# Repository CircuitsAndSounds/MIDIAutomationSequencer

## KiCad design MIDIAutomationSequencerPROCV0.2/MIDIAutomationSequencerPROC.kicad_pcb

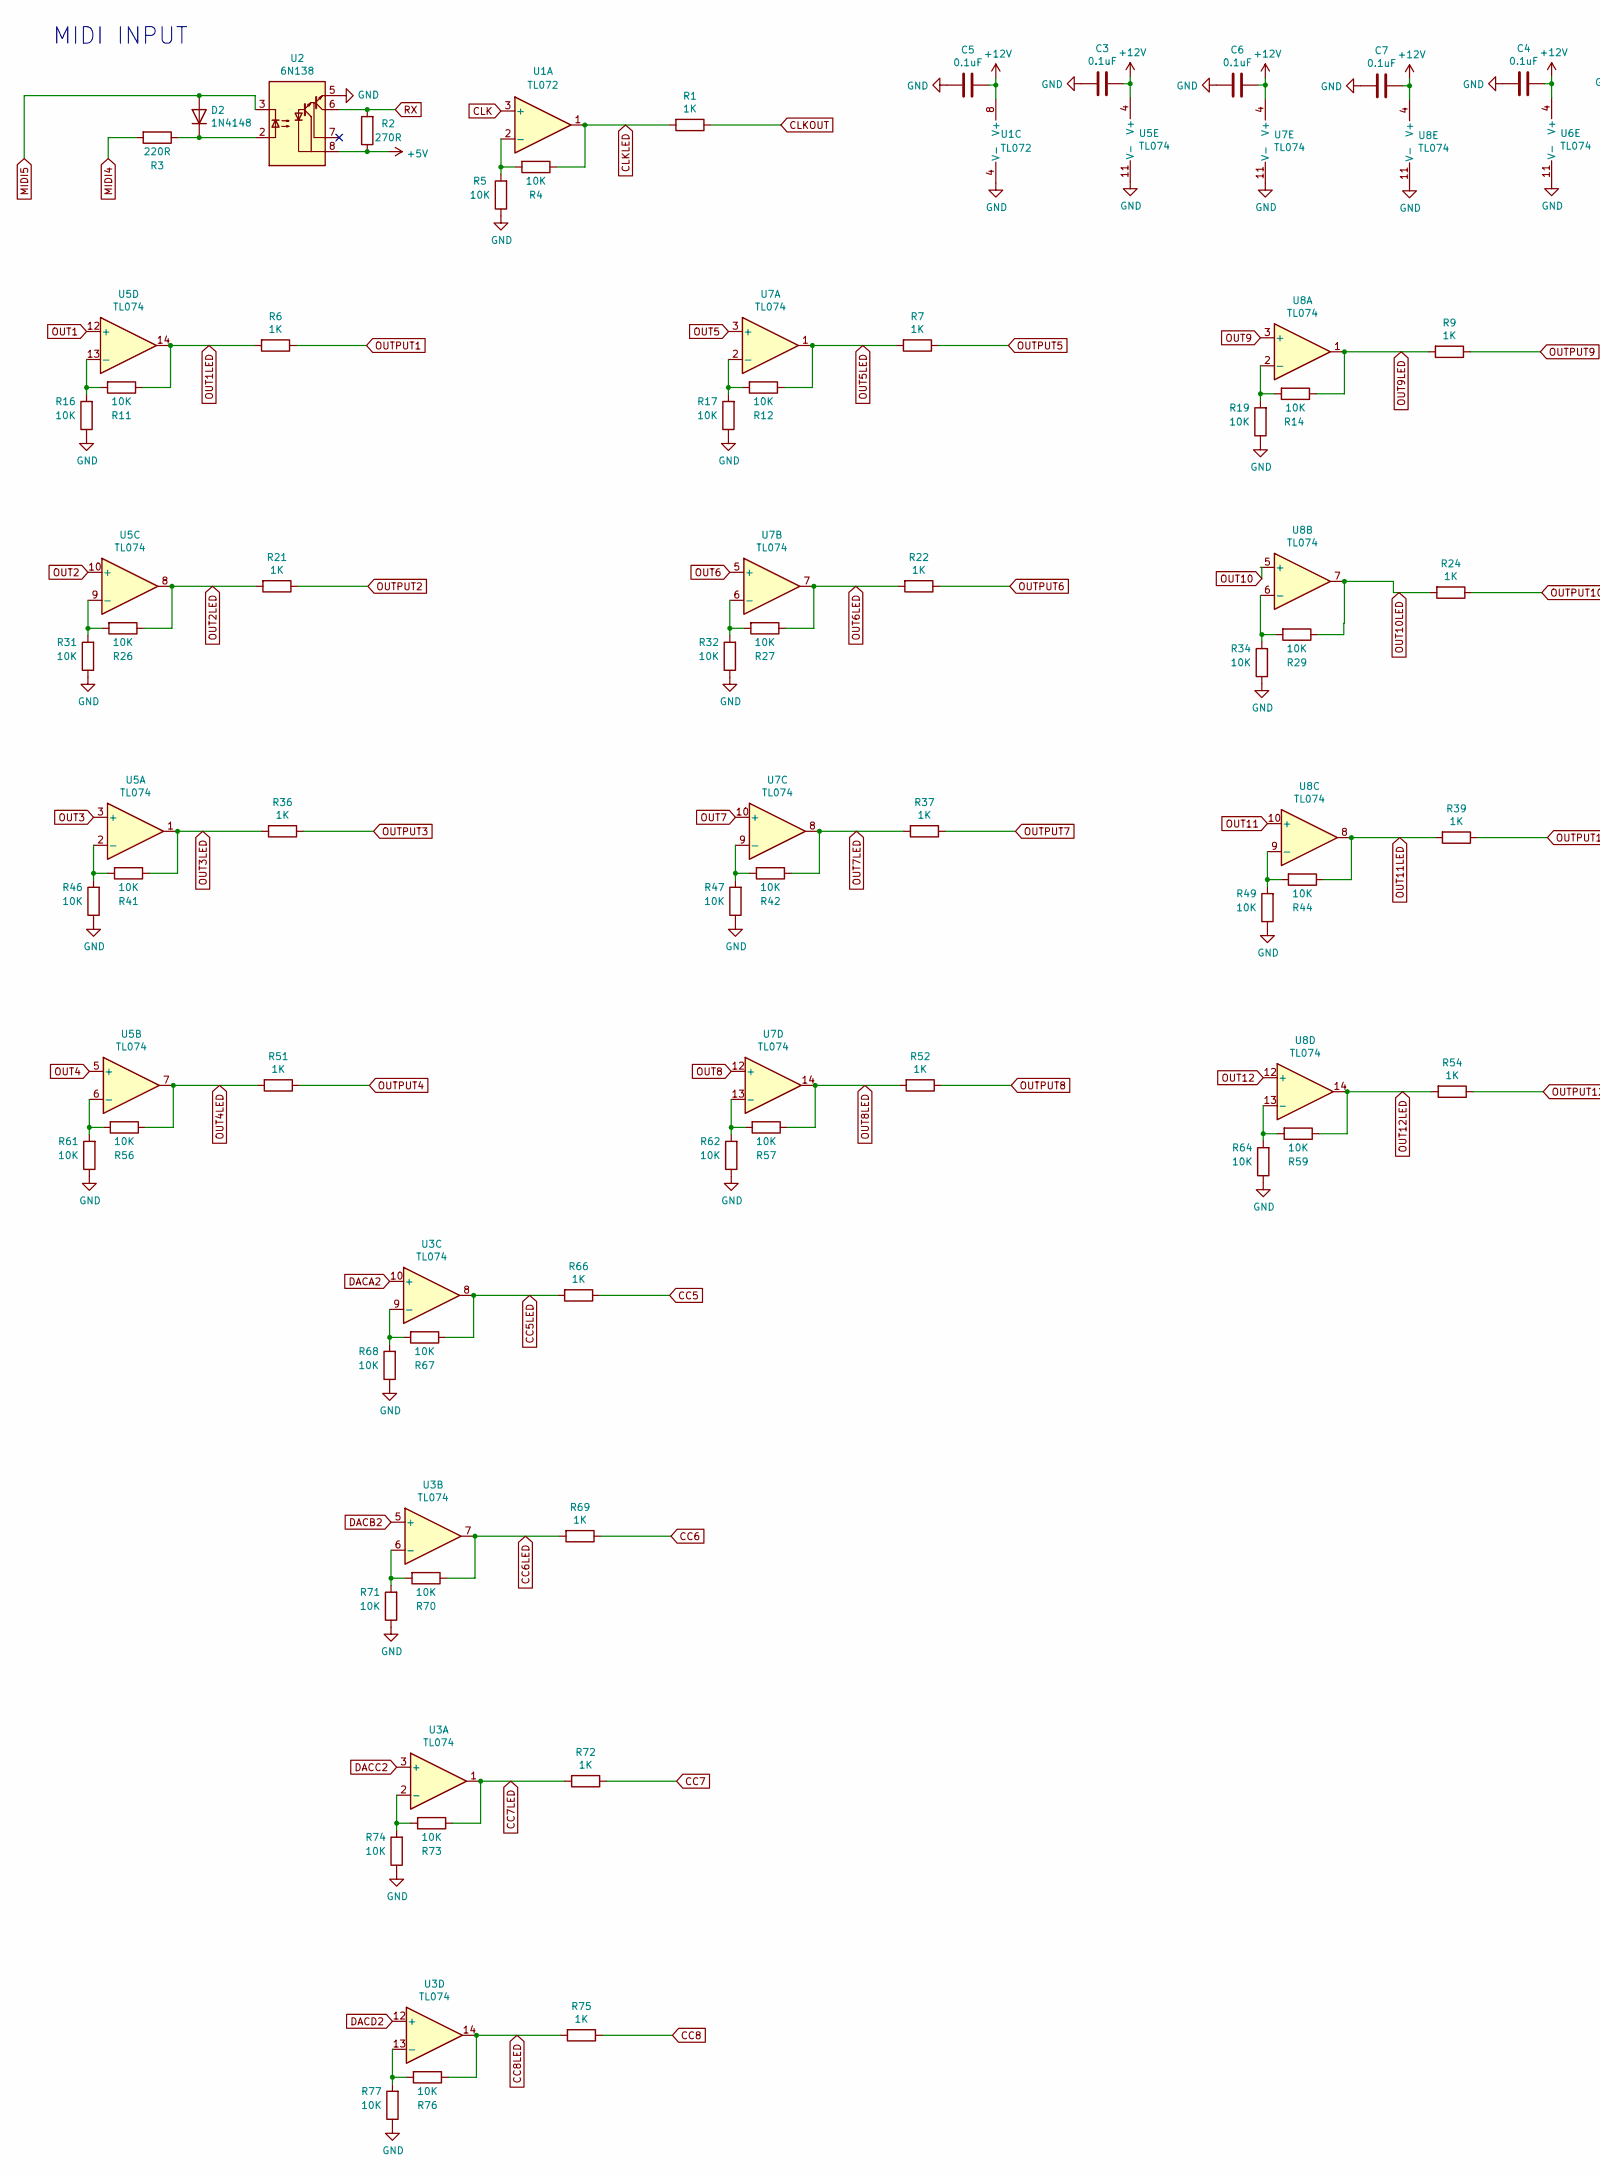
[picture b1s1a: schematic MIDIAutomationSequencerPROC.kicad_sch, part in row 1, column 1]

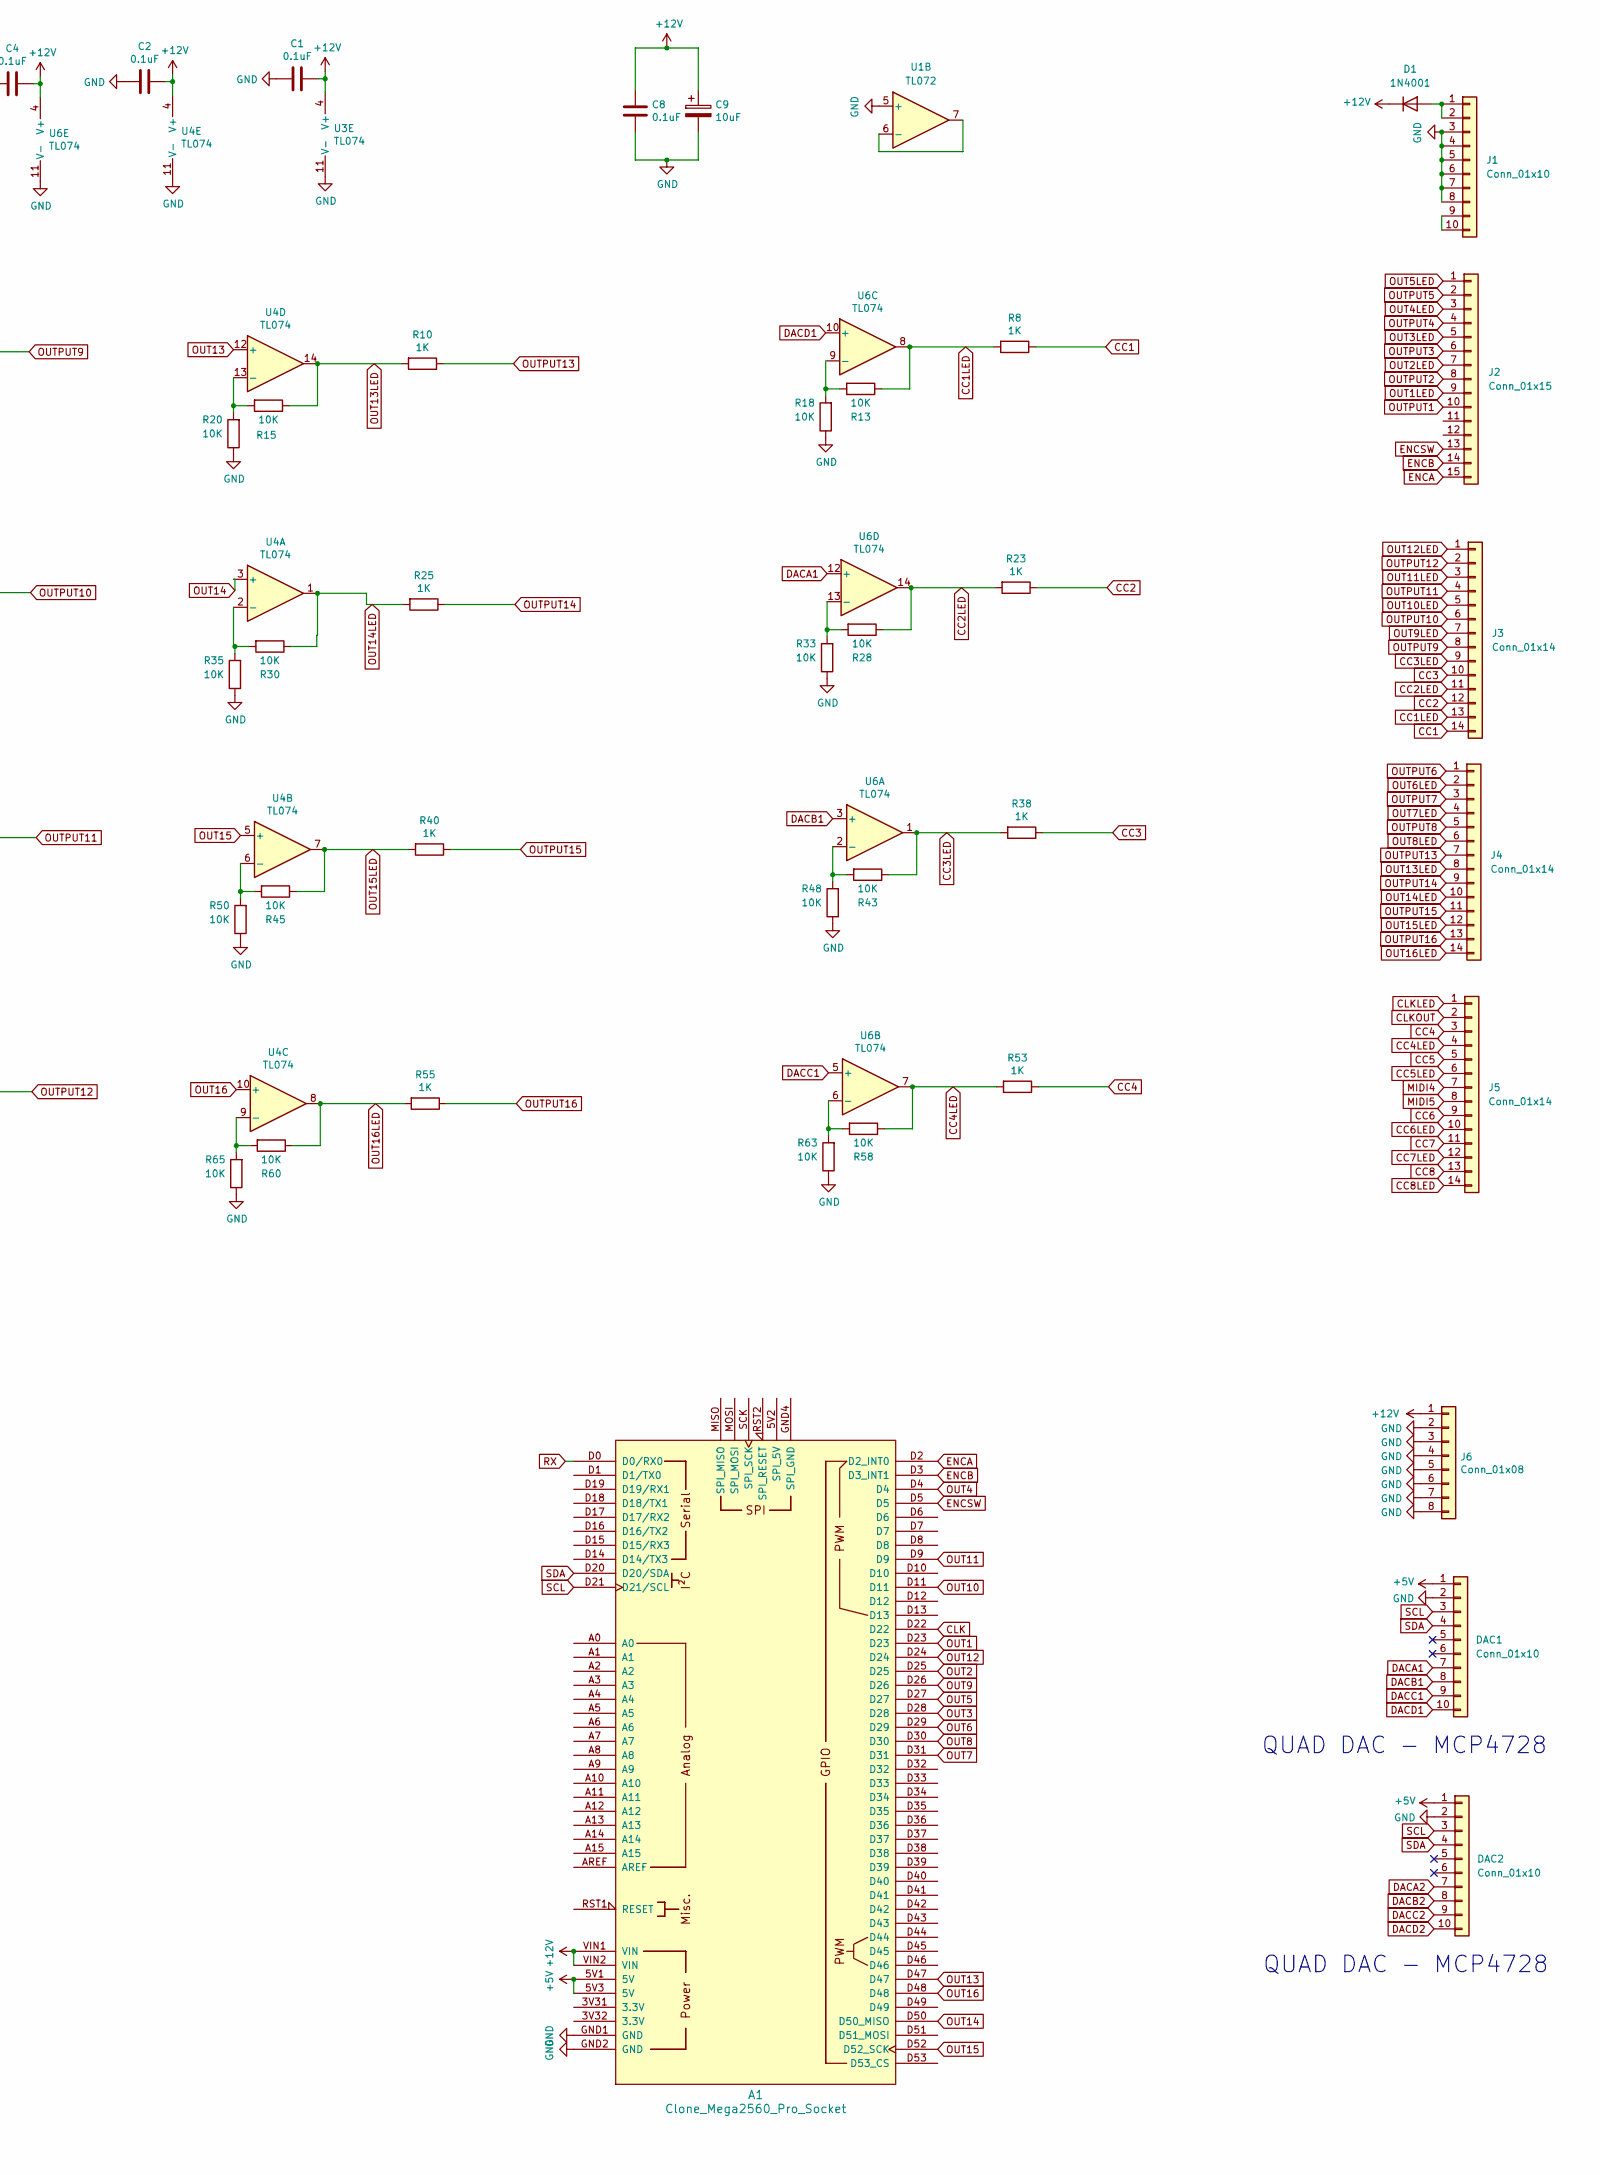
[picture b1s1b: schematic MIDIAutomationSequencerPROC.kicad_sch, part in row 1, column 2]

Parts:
A1: Clone_Mega2560_Pro_Socket
C1, C2, C3, C4, C5, C6, C7, C8: 0.1uF; C_Rect_L7.0mm_W2.0mm_P5.00mm
C9: 10uF; CP_Radial_D5.0mm_P2.50mm
D1: 1N4001; D_DO-41_SOD81_P10.16mm_Horizontal
D2: 1N4148; D_DO-35_SOD27_P2.54mm_Vertical_AnodeUp
DAC1, DAC2: Conn_01x10; PinHeader_1x10_P2.54mm_Vertical
J1: Conn_01x10; PinHeader_2x05_P2.54mm_Vertical
J2: Conn_01x15; PinHeader_1x15_P2.54mm_Vertical
J3, J4, J5: Conn_01x14; PinHeader_1x14_P2.54mm_Vertical
J6: Conn_01x08; PinHeader_1x08_P2.54mm_Vertical
R1, R6, R7, R8, R9, R10, R21, R22, R23, R24, R25, R36, R37, R38, R39, R40, R51, R52, R53, R54, R55, R66, R69, R72, R75: 1K; R_Axial_DIN0207_L6.3mm_D2.5mm_P2.54mm_Vertical
R2: 270R; R_Axial_DIN0207_L6.3mm_D2.5mm_P2.54mm_Vertical
R3: 220R; R_Axial_DIN0207_L6.3mm_D2.5mm_P2.54mm_Vertical
R4, R5, R11, R12, R13, R14, R15, R16, R17, R18, R19, R20, R26, R27, R28, R29, R30, R31, R32, R33, R34, R35, R41, R42, R43, R44, R45, R46, R47, R48, R49, R50, R56, R57, R58, R59, R60, R61, R62, R63, R64, R65, R67, R68, R70, R71, R73, R74, R76, R77: 10K; R_Axial_DIN0207_L6.3mm_D2.5mm_P2.54mm_Vertical
U1: TL072; DIP-8_W7.62mm
U2: 6N138; DIP-8_W7.62mm
U3, U4, U5, U6, U7, U8: TL074; DIP-14_W7.62mm

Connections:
+5V: A1.5V1 (5V), A1.5V3 (5V), DAC1.1, DAC2.1, R2.1, U2.8 (VCC)
+12V: A1.VIN1 (VIN), A1.VIN2 (VIN), C1.1, C2.1, C3.1, C4.1, C5.1, C6.1, C7.1, C8.1, C9.1, D1.1 (K), J6.1, U1.8 (V+), U3.4 (V+), U4.4 (V+), U5.4 (V+), U6.4 (V+), U7.4 (V+), U8.4 (V+)
CC1: J3.14, R8.1
CC1LED: J3.13, R8.2, R13.1, U6.8
CC2: J3.12, R23.1
CC2LED: J3.11, R23.2, R28.1, U6.14
CC3: J3.10, R38.1
CC3LED: J3.9, R38.2, R43.1, U6.1
CC4: J5.3, R53.1
CC4LED: J5.4, R53.2, R58.1, U6.7
CC5: J5.5, R66.1
CC5LED: J5.6, R66.2, R67.1, U3.8
CC6: J5.9, R69.1
CC6LED: J5.10, R69.2, R70.1, U3.7
CC7: J5.11, R72.1
CC7LED: J5.12, R72.2, R73.1, U3.1
CC8: J5.13, R75.1
CC8LED: J5.14, R75.2, R76.1, U3.14
CLK: A1.D22, U1.3 (+)
CLKLED: J5.1, R1.2, R4.1, U1.1
CLKOUT: J5.2, R1.1
DACA1: DAC1.7, U6.12 (+)
DACA2: DAC2.7, U3.10 (+)
DACB1: DAC1.8, U6.3 (+)
DACB2: DAC2.8, U3.5 (+)
DACC1: DAC1.9, U6.5 (+)
DACC2: DAC2.9, U3.3 (+)
DACD1: DAC1.10, U6.10 (+)
DACD2: DAC2.10, U3.12 (+)
ENCA: A1.D2 (D2_INT0), J2.15
ENCB: A1.D3 (D3_INT1), J2.14
ENCSW: A1.D5, J2.13
GND: A1.GND1 (GND), A1.GND2 (GND), C1.2, C2.2, C3.2, C4.2, C5.2, C6.2, C7.2, C8.2, C9.2, DAC1.2, DAC2.2, J1.3, J1.4, J1.5, J1.6, J1.7, J1.8, J6.2, J6.3, J6.4, J6.5, J6.6, J6.7, J6.8, R5.1, R16.1, R17.1, R18.1, R19.1, R20.1, R31.1, R32.1, R33.1, R34.1, R35.1, R46.1, R47.1, R48.1, R49.1, R50.1, R61.1, R62.1, R63.1, R64.1, R65.1, R68.1, R71.1, R74.1, R77.1, U1.4 (V-), U1.5 (+), U2.5 (GND), U3.11 (V-), U4.11 (V-), U5.11 (V-), U6.11 (V-), U7.11 (V-), U8.11 (V-)
MIDI4: J5.7, R3.2
MIDI5: D2.2 (A), J5.8, U2.3 (C2)
unnamed: D1.2 (A), J1.1, J1.2
unnamed: D2.1 (K), R3.1, U2.2 (C1)
unnamed: J1.9, J1.10
unnamed: R4.2, R5.2, U1.2 (-)
unnamed: U1.6 (-), U1.7
unnamed: R73.2, R74.2, U3.2 (-)
unnamed: R70.2, R71.2, U3.6 (-)
unnamed: R67.2, R68.2, U3.9 (-)
unnamed: R76.2, R77.2, U3.13 (-)
unnamed: R30.2, R35.2, U4.2 (-)
unnamed: R45.2, R50.2, U4.6 (-)
unnamed: R60.2, R65.2, U4.9 (-)
unnamed: R15.2, R20.2, U4.13 (-)
unnamed: R41.2, R46.2, U5.2 (-)
unnamed: R56.2, R61.2, U5.6 (-)
unnamed: R26.2, R31.2, U5.9 (-)
unnamed: R11.2, R16.2, U5.13 (-)
unnamed: R43.2, R48.2, U6.2 (-)
unnamed: R58.2, R63.2, U6.6 (-)
unnamed: R13.2, R18.2, U6.9 (-)
unnamed: R28.2, R33.2, U6.13 (-)
unnamed: R12.2, R17.2, U7.2 (-)
unnamed: R27.2, R32.2, U7.6 (-)
unnamed: R42.2, R47.2, U7.9 (-)
unnamed: R57.2, R62.2, U7.13 (-)
unnamed: R14.2, R19.2, U8.2 (-)
unnamed: R29.2, R34.2, U8.6 (-)
unnamed: R44.2, R49.2, U8.9 (-)
unnamed: R59.2, R64.2, U8.13 (-)
OUT1: A1.D23, U5.12 (+)
OUT1LED: J2.9, R6.2, R11.1, U5.14
OUT2: A1.D25, U5.10 (+)
OUT2LED: J2.7, R21.2, R26.1, U5.8
OUT3: A1.D28, U5.3 (+)
OUT3LED: J2.5, R36.2, R41.1, U5.1
OUT4: A1.D4, U5.5 (+)
OUT4LED: J2.3, R51.2, R56.1, U5.7
OUT5: A1.D27, U7.3 (+)
OUT5LED: J2.1, R7.2, R12.1, U7.1
OUT6: A1.D29, U7.5 (+)
OUT6LED: J4.2, R22.2, R27.1, U7.7
OUT7: A1.D31, U7.10 (+)
OUT7LED: J4.4, R37.2, R42.1, U7.8
OUT8: A1.D30, U7.12 (+)
OUT8LED: J4.6, R52.2, R57.1, U7.14
OUT9: A1.D26, U8.3 (+)
OUT9LED: J3.7, R9.2, R14.1, U8.1
OUT10: A1.D11, U8.5 (+)
OUT10LED: J3.5, R24.2, R29.1, U8.7
OUT11: A1.D9, U8.10 (+)
OUT11LED: J3.3, R39.2, R44.1, U8.8
OUT12: A1.D24, U8.12 (+)
OUT12LED: J3.1, R54.2, R59.1, U8.14
OUT13: A1.D47, U4.12 (+)
OUT13LED: J4.8, R10.2, R15.1, U4.14
OUT14: A1.D50 (D50_MISO), U4.3 (+)
OUT14LED: J4.10, R25.2, R30.1, U4.1
OUT15: A1.D52 (D52_SCK), U4.5 (+)
OUT15LED: J4.12, R40.2, R45.1, U4.7
OUT16: A1.D48, U4.10 (+)
OUT16LED: J4.14, R55.2, R60.1, U4.8
OUTPUT1: J2.10, R6.1
OUTPUT2: J2.8, R21.1
OUTPUT3: J2.6, R36.1
OUTPUT4: J2.4, R51.1
OUTPUT5: J2.2, R7.1
OUTPUT6: J4.1, R22.1
OUTPUT7: J4.3, R37.1
OUTPUT8: J4.5, R52.1
OUTPUT9: J3.8, R9.1
OUTPUT10: J3.6, R24.1
OUTPUT11: J3.4, R39.1
OUTPUT12: J3.2, R54.1
OUTPUT13: J4.7, R10.1
OUTPUT14: J4.9, R25.1
OUTPUT15: J4.11, R40.1
OUTPUT16: J4.13, R55.1
RX: A1.D0 (D0/RX0), R2.2, U2.6 (VO2)
SCL: A1.D21 (D21/SCL), DAC1.3, DAC2.3
SDA: A1.D20 (D20/SDA), DAC1.4, DAC2.4

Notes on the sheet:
QUAD DAC - MCP4728
MIDI INPUT

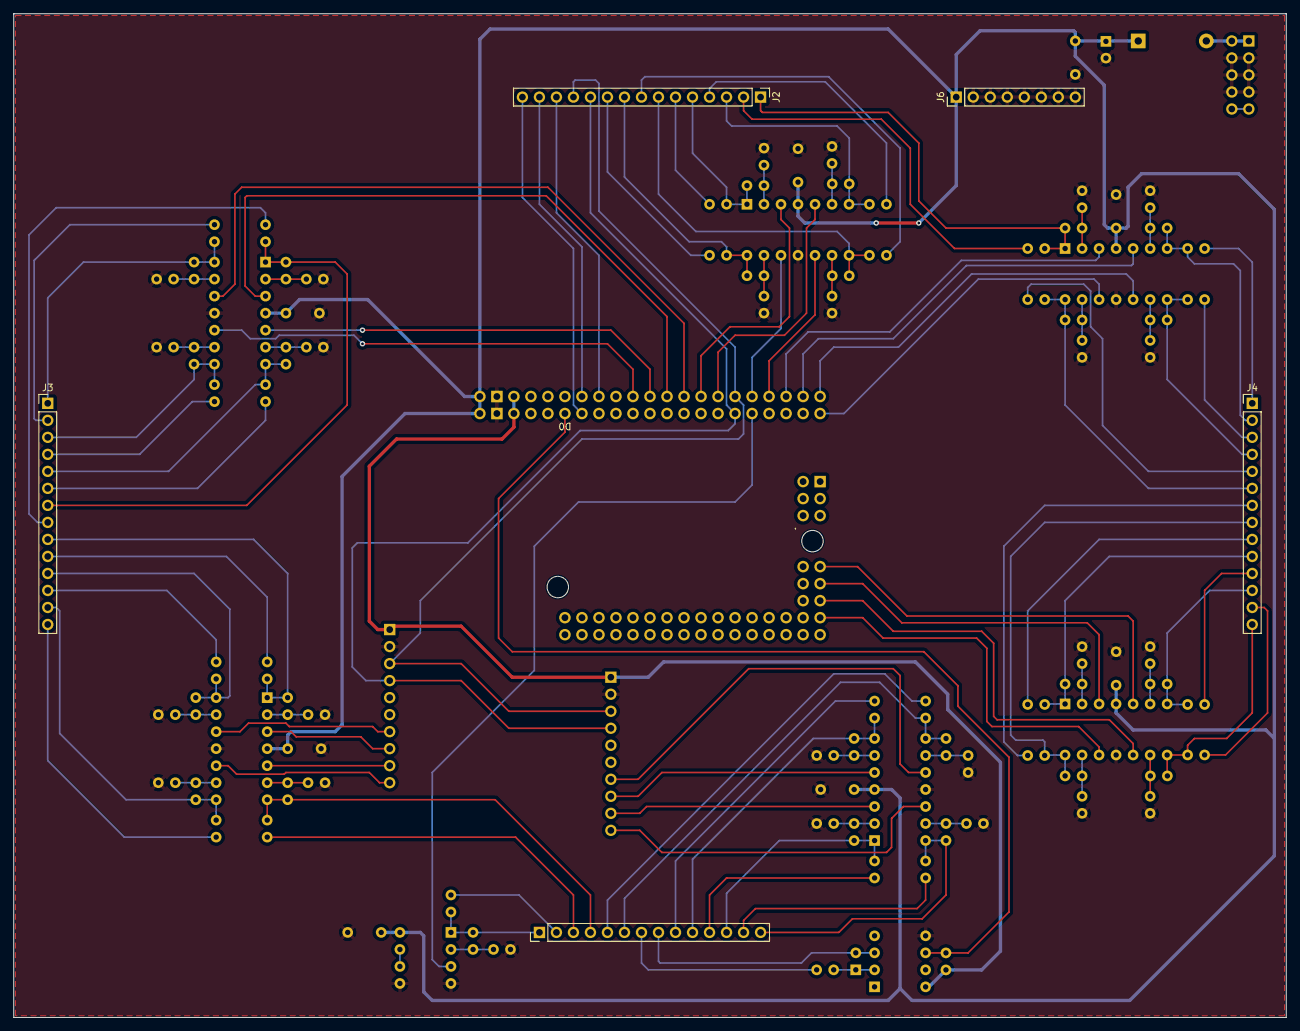
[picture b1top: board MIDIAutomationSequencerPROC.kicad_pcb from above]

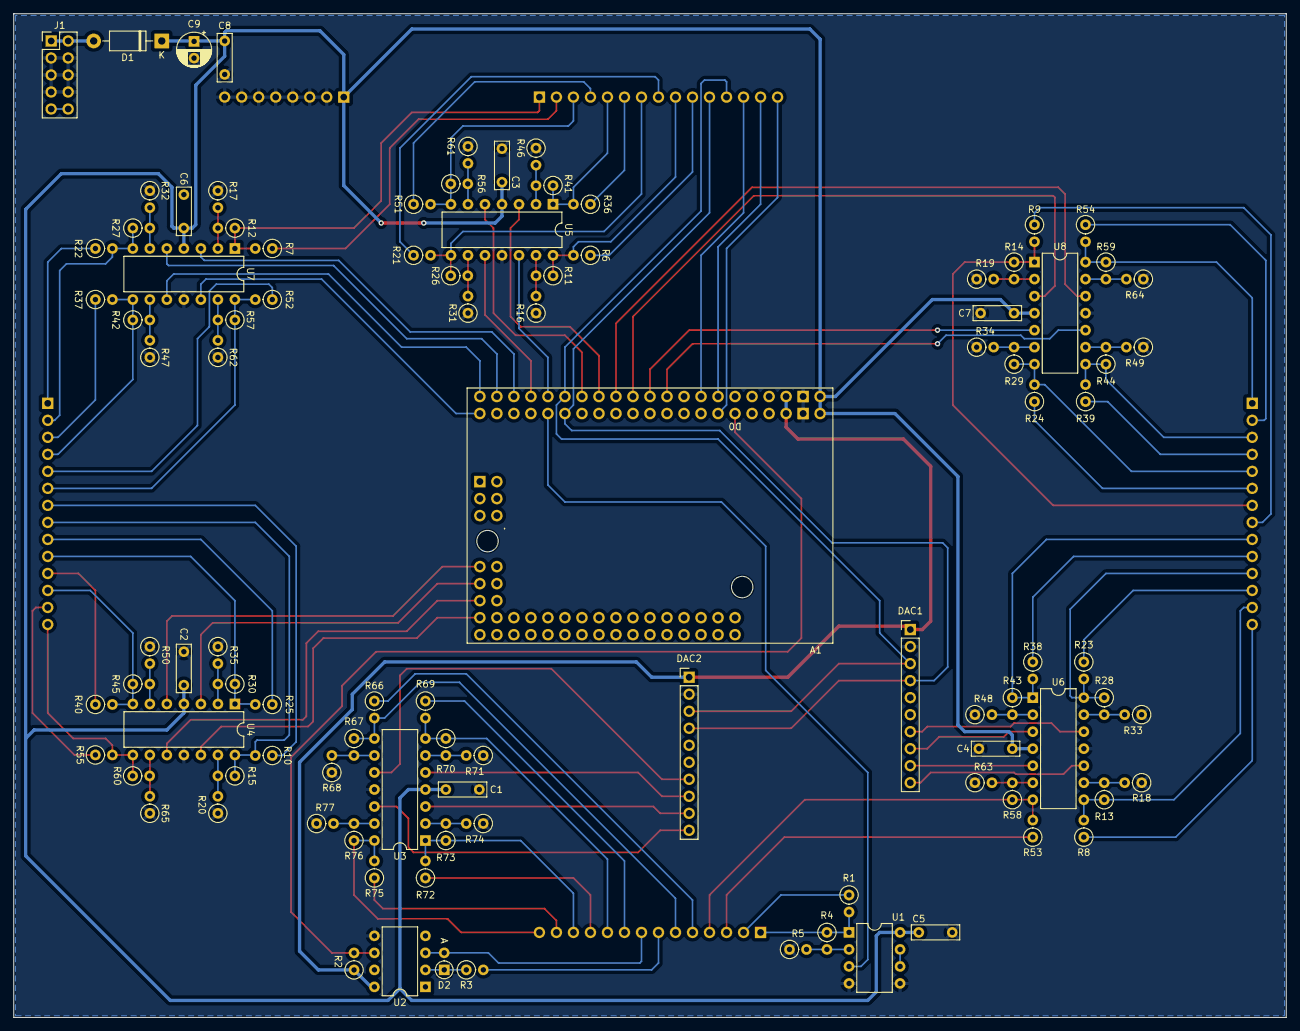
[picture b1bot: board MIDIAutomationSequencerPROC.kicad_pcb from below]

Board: 2 copper layers, 190.0 x 149.9 mm, 105 parts (100 on the bottom side), 115 nets.

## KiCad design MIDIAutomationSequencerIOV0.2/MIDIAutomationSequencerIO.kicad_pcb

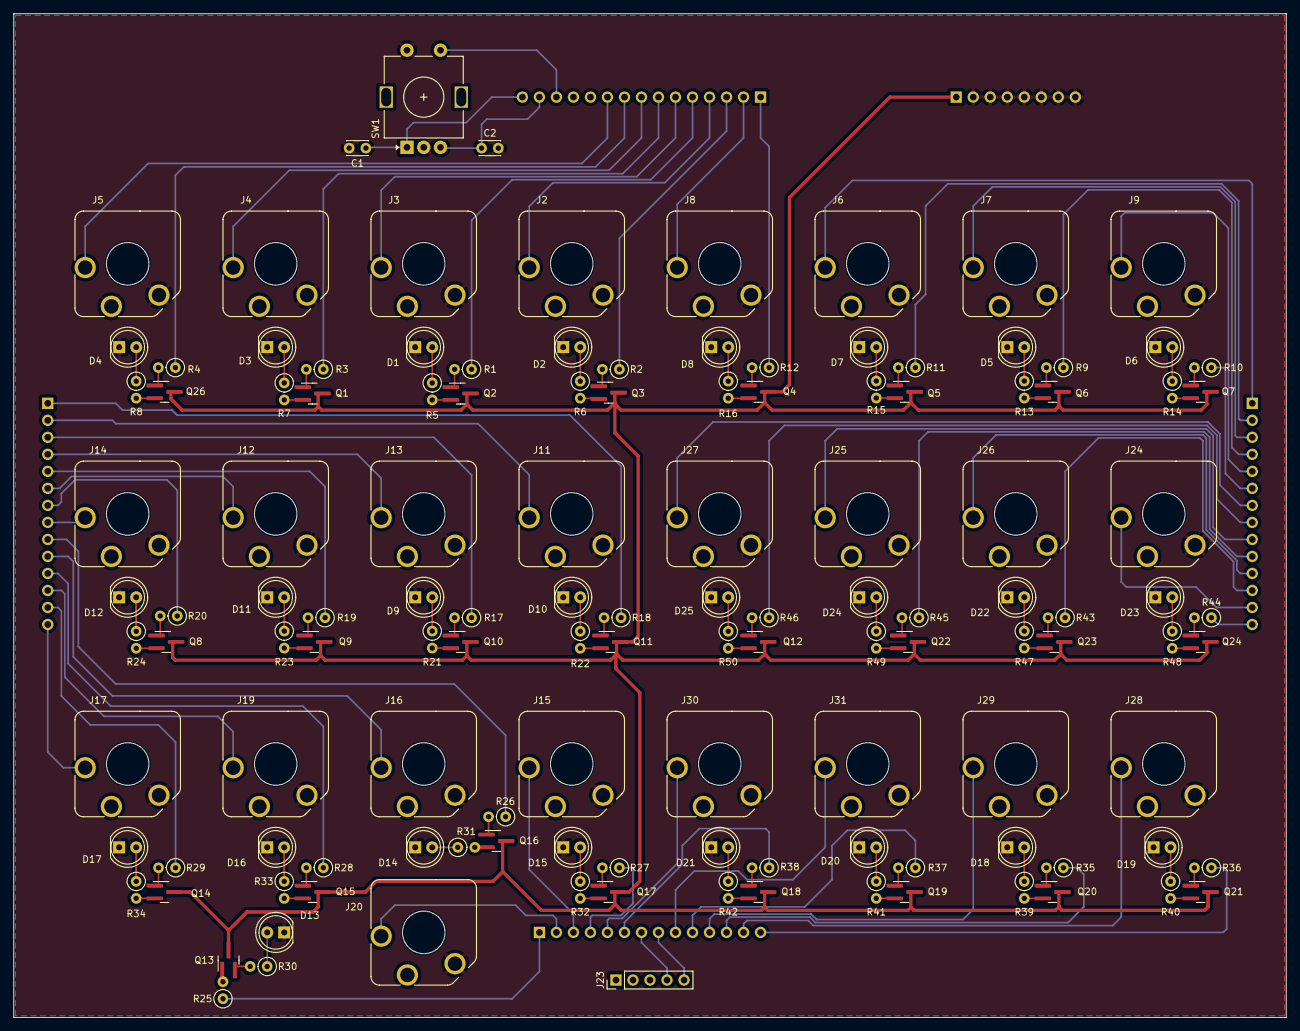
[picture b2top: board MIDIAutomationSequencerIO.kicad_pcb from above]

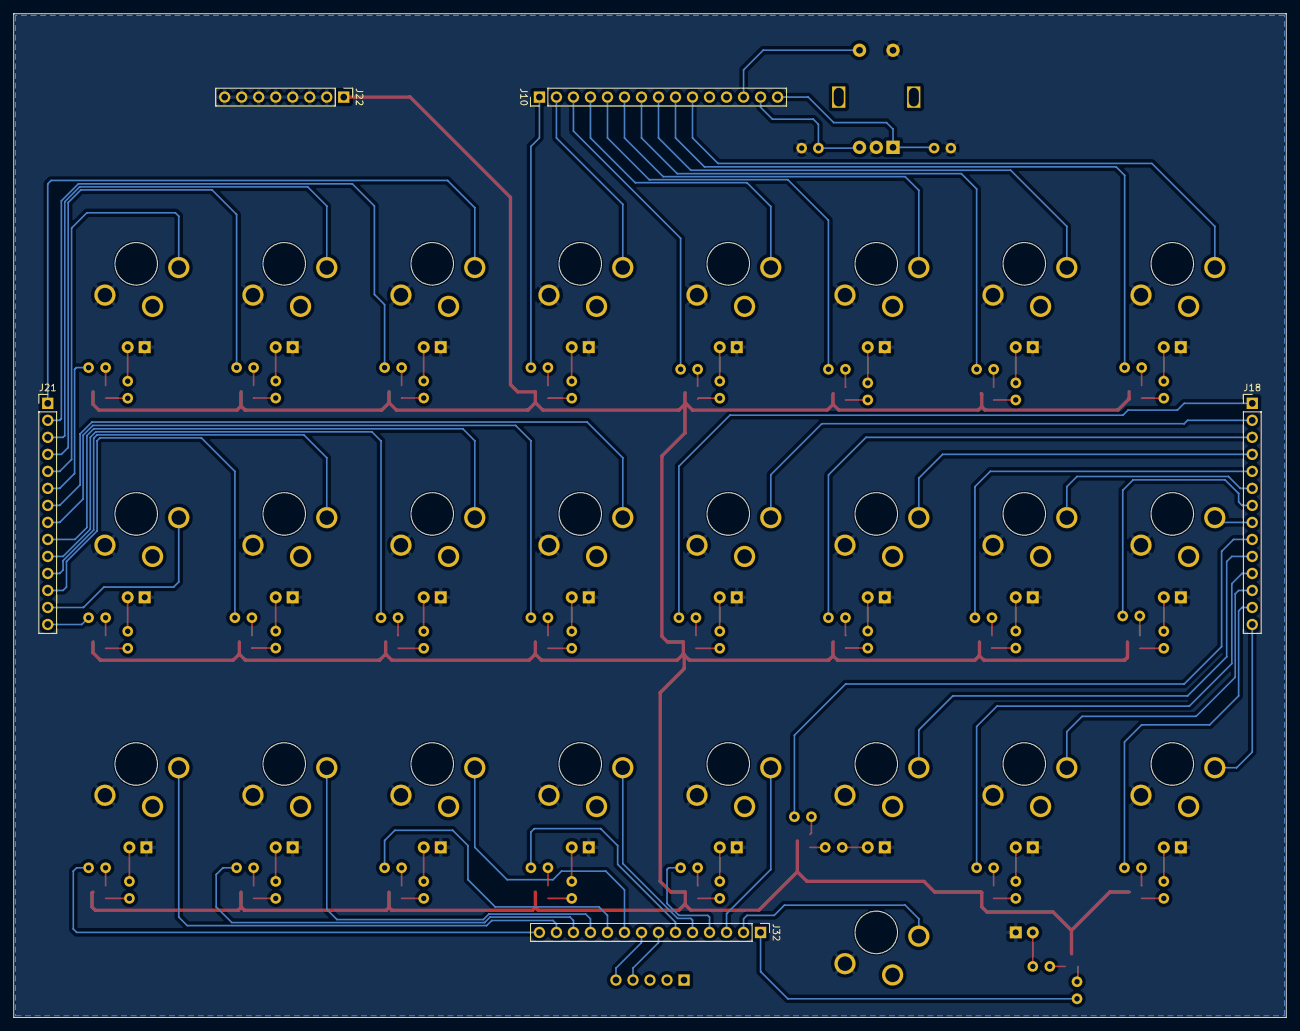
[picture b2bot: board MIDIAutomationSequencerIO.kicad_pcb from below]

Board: 2 copper layers, 190.0 x 149.9 mm, 134 parts (5 on the bottom side), 132 nets.

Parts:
C1, C2: 0.01uF; C_Disc_D3.0mm_W2.0mm_P2.50mm
D1, D2, D3, D4, D5, D6, D7, D8, D9, D10, D11, D12, D13, D14, D15, D16, D17, D18, D19, D20, D21, D22, D23, D24, D25: LED; LED_D5.0mm
J2: OUT4; SWITCHCRAFT_112APCX
J3: OUT3; SWITCHCRAFT_112APCX
J4: OUT2; SWITCHCRAFT_112APCX
J5: OUT1; SWITCHCRAFT_112APCX
J6: OUT6; SWITCHCRAFT_112APCX
J7: OUT7; SWITCHCRAFT_112APCX
J8: OUT5; SWITCHCRAFT_112APCX
J9: OUT8; SWITCHCRAFT_112APCX
J10: Conn_01x15; PinHeader_1x15_P2.54mm_Vertical
J11: OUT12; SWITCHCRAFT_112APCX
J12: OUT10; SWITCHCRAFT_112APCX
J13: OUT11; SWITCHCRAFT_112APCX
J14: OUT9; SWITCHCRAFT_112APCX
J15, J20, J28: TRIGGEROUT; SWITCHCRAFT_112APCX
J16, J29: G8OUT; SWITCHCRAFT_112APCX
J17, J30: V/OCT; SWITCHCRAFT_112APCX
J18, J21, J32: Conn_01x14; PinHeader_1x14_P2.54mm_Vertical
J19, J31: PITCHBEND; SWITCHCRAFT_112APCX
J22: Conn_01x08; PinHeader_1x08_P2.54mm_Vertical
J23: DIN-5_180degree; PinHeader_1x05_P2.54mm_Vertical
J24: OUT16; SWITCHCRAFT_112APCX
J25: OUT14; SWITCHCRAFT_112APCX
J26: OUT15; SWITCHCRAFT_112APCX
J27: OUT13; SWITCHCRAFT_112APCX
Q1, Q2, Q3, Q4, Q5, Q6, Q7, Q8, Q9, Q10, Q11, Q12, Q13, Q14, Q15, Q16, Q17, Q18, Q19, Q20, Q21, Q22, Q23, Q24, Q26: MMBT3904; SOT-23-WIDE
R1, R2, R3, R4, R9, R10, R11, R12, R17, R18, R19, R20, R25, R26, R27, R28, R29, R35, R36, R37, R38, R43, R44, R45, R46: 10K; R_Axial_DIN0207_L6.3mm_D2.5mm_P2.54mm_Vertical
R5, R6, R7, R8, R13, R14, R15, R16, R21, R22, R23, R24, R30, R31, R32, R33, R34, R39, R40, R41, R42, R47, R48, R49, R50: 1K; R_Axial_DIN0207_L6.3mm_D2.5mm_P2.54mm_Vertical
SW1: RotaryEncoder_Switch; RotaryEncoder_Alps_EC11E-Switch_Vertical_H20mm

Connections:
+12V: J22.1, Q1.3 (C), Q2.3 (C), Q3.3 (C), Q4.3 (C), Q5.3 (C), Q6.3 (C), Q7.3 (C), Q8.3 (C), Q9.3 (C), Q10.3 (C), Q11.3 (C), Q12.3 (C), Q13.3 (C), Q14.3 (C), Q15.3 (C), Q16.3 (C), Q17.3 (C), Q18.3 (C), Q19.3 (C), Q20.3 (C), Q21.3 (C), Q22.3 (C), Q23.3 (C), Q24.3 (C), Q26.3 (C)
CC1: J17.T, J18.14
CC1LED: J18.13, R29.1
CC2: J18.12, J19.T
CC2LED: J18.11, R28.1
CC3: J16.T, J18.10
CC3LED: J18.9, R26.1
CC4: J15.T, J32.3
CC4LED: J32.4, R27.1
CC5: J30.T, J32.5
CC5LED: J32.6, R38.1
CC6: J31.T, J32.9
CC6LED: J32.10, R37.1
CC7: J29.T, J32.11
CC7LED: J32.12, R35.1
CC8: J28.T, J32.13
CC8LED: J32.14, R36.1
CLKLED: J32.1, R25.1
CLKOUT: J20.T, J32.2
ENCA: C1.1, J10.15, SW1.A
ENCB: C2.1, J10.14, SW1.B
ENCSW: J10.13, SW1.S1
GND: C1.2, C2.2, D1.1 (K), D2.1 (K), D3.1 (K), D4.1 (K), D5.1 (K), D6.1 (K), D7.1 (K), D8.1 (K), D9.1 (K), D10.1 (K), D11.1 (K), D12.1 (K), D13.1 (K), D14.1 (K), D15.1 (K), D16.1 (K), D17.1 (K), D18.1 (K), D19.1 (K), D20.1 (K), D21.1 (K), D22.1 (K), D23.1 (K), D24.1 (K), D25.1 (K), J2.S, J3.S, J4.S, J5.S, J6.S, J7.S, J8.S, J9.S, J11.S, J12.S, J13.S, J14.S, J15.S, J16.S, J17.S, J19.S, J20.S, J22.2, J22.3, J22.4, J22.5, J22.6, J22.7, J22.8, J24.S, J25.S, J26.S, J27.S, J28.S, J29.S, J30.S, J31.S, SW1.C, SW1.S2
MIDI4: J23.4, J32.7
MIDI5: J23.5, J32.8
unnamed: D1.2 (A), R5.1
unnamed: D2.2 (A), R6.1
unnamed: D3.2 (A), R7.1
unnamed: D4.2 (A), R8.1
unnamed: D5.2 (A), R13.1
unnamed: D6.2 (A), R14.1
unnamed: D7.2 (A), R15.1
unnamed: D8.2 (A), R16.1
unnamed: D9.2 (A), R21.1
unnamed: D10.2 (A), R22.1
unnamed: D11.2 (A), R23.1
unnamed: D12.2 (A), R24.1
unnamed: D13.2 (A), R30.1
unnamed: D14.2 (A), R31.1
unnamed: D15.2 (A), R32.1
unnamed: D16.2 (A), R33.1
unnamed: D17.2 (A), R34.1
unnamed: D18.2 (A), R39.1
unnamed: D19.2 (A), R40.1
unnamed: D20.2 (A), R41.1
unnamed: D21.2 (A), R42.1
unnamed: D22.2 (A), R47.1
unnamed: D23.2 (A), R48.1
unnamed: D24.2 (A), R49.1
unnamed: D25.2 (A), R50.1
unnamed: Q1.1 (B), R3.2
unnamed: Q1.2 (E), R7.2
unnamed: Q2.1 (B), R1.2
unnamed: Q2.2 (E), R5.2
unnamed: Q3.1 (B), R2.2
unnamed: Q3.2 (E), R6.2
unnamed: Q4.1 (B), R12.2
unnamed: Q4.2 (E), R16.2
unnamed: Q5.1 (B), R11.2
unnamed: Q5.2 (E), R15.2
unnamed: Q6.1 (B), R9.2
unnamed: Q6.2 (E), R13.2
unnamed: Q7.1 (B), R10.2
unnamed: Q7.2 (E), R14.2
unnamed: Q8.1 (B), R20.2
unnamed: Q8.2 (E), R24.2
unnamed: Q9.1 (B), R19.2
unnamed: Q9.2 (E), R23.2
unnamed: Q10.1 (B), R17.2
unnamed: Q10.2 (E), R21.2
unnamed: Q11.1 (B), R18.2
unnamed: Q11.2 (E), R22.2
unnamed: Q12.1 (B), R46.2
unnamed: Q12.2 (E), R50.2
unnamed: Q13.1 (B), R25.2
unnamed: Q13.2 (E), R30.2
unnamed: Q14.1 (B), R29.2
unnamed: Q14.2 (E), R34.2
unnamed: Q15.1 (B), R28.2
unnamed: Q15.2 (E), R33.2
unnamed: Q16.1 (B), R26.2
unnamed: Q16.2 (E), R31.2
unnamed: Q17.1 (B), R27.2
unnamed: Q17.2 (E), R32.2
unnamed: Q18.1 (B), R38.2
unnamed: Q18.2 (E), R42.2
unnamed: Q19.1 (B), R37.2
unnamed: Q19.2 (E), R41.2
unnamed: Q20.1 (B), R35.2
unnamed: Q20.2 (E), R39.2
unnamed: Q21.1 (B), R36.2
unnamed: Q21.2 (E), R40.2
unnamed: Q22.1 (B), R45.2
unnamed: Q22.2 (E), R49.2
unnamed: Q23.1 (B), R43.2
unnamed: Q23.2 (E), R47.2
unnamed: Q24.1 (B), R44.2
unnamed: Q24.2 (E), R48.2
unnamed: Q26.1 (B), R4.2
unnamed: Q26.2 (E), R8.2
OUT1LED: J10.9, R4.1
OUT2LED: J10.7, R3.1
OUT3LED: J10.5, R1.1
OUT4LED: J10.3, R2.1
OUT5LED: J10.1, R12.1
OUT6LED: J21.2, R11.1
OUT7LED: J21.4, R9.1
OUT8LED: J21.6, R10.1
OUT9LED: J18.7, R20.1
OUT10LED: J18.5, R19.1
OUT11LED: J18.3, R17.1
OUT12LED: J18.1, R18.1
OUT13LED: J21.8, R46.1
OUT14LED: J21.10, R45.1
OUT15LED: J21.12, R43.1
OUT16LED: J21.14, R44.1
OUTPUT1: J5.T, J10.10
OUTPUT2: J4.T, J10.8
OUTPUT3: J3.T, J10.6
OUTPUT4: J2.T, J10.4
OUTPUT5: J8.T, J10.2
OUTPUT6: J6.T, J21.1
OUTPUT7: J7.T, J21.3
OUTPUT8: J9.T, J21.5
OUTPUT9: J14.T, J18.8
OUTPUT10: J12.T, J18.6
OUTPUT11: J13.T, J18.4
OUTPUT12: J11.T, J18.2
OUTPUT13: J21.7, J27.T
OUTPUT14: J21.9, J25.T
OUTPUT15: J21.11, J26.T
OUTPUT16: J21.13, J24.T
